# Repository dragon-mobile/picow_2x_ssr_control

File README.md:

# picow_ssr_control

<br/>

<br/>

The Raspberry Pi Pico W 2x Solid State Relay Controller is primarily meant to be
used with an open hardware solid state relay PCBs that is being co-developed
alongside this project as part of my Dragon Mobile GitHub organization to make
useful hardware with associated firmware and software for the tiny home, van
life and maker communities.

## Visual 3D examples

Top view<br/>
<br/>
Bottom view<br/>
<br/>

## Description

___Outdated___

~~The board consist of four main electronic sections: Power In / Control Out,
Power Management / Regulation, Manual Control,
and the PicoW Control / Drivers.
There is one mechanical section as well: Mounting Holes.~~

## Contributing

Contributors are welcome.
Please note that this project has a [Contributor Covenant Code of Conduct].
By participating in this project you agree to abide by its terms.

All intentionally contributed hardware will be considered to be contributed
under the [CERN] license without any additional terms or conditions.

All intentionally contributed code will be considered to be contributed
under a [MIT] license without any additional terms or conditions.
Please include your information in a comment on all code files for the copyright
etc.

All intentionally contributed documentation, CAD files and libraries, footprints,
artwork or non-code text like this README etc. will be considered to be
contributed under the same [CC-BY-SA] license without any additional terms or
conditions.

Pull requests are always welcome. For major changes, please open an issue first
to discuss what you would like to change.
Please make sure to update or add tests as appropriate for all software changes.

## Licenses

<br/>

All hardware is licensed under the

  * [CERN] - CERN-OHL-W-2.0
  
You can find a copy of the CERN Open Hardware License - Weakly-reciprocal v2.0
in the [LICENSE-CERN-OHL-W-2] file and the how-to guide in the
[CERN-HOWTO_GUIDE] file.

All code is licensed under the

  * [MIT] - MIT License

You can find a copy of the license in the [LICENSE-MIT] file.

All documentation like this README is licensed under the Creative Commons
Attribution-ShareAlike 4.0 International License (CC-BY-SA).

All original CAD files and libraries, footprints, and artwork are also licensed
under the
Creative Commons Attribution-ShareAlike 4.0 International License (CC-BY-SA).
You can find a copy of the [CC-BY-SA] license in the [LICENSE-CC-BY-SA] file.

If after reading the above license files, how-tos, and related FAQs on the
linked license sites on how they apply to the project please either open an
issue or contact me (Michael Cummings) via my Github email and I will try
to guided you through my understanding of how it works.

[CC-BY-SA]: http://creativecommons.org/licenses/by-sa/4.0/
[CERN]: https://ohwr.org/project/cernohl/wikis/Documents/CERN-OHL-version-2
[CERN-HOWTO_GUIDE]: docs/cern_ohl_w_v2_howto.pdf
[Contributor Covenant Code of Conduct]: CODE_OF_CONDUCT.md 
[LICENSE-CC-BY-SA]: LICENSE-CC-BY-SA
[LICENSE-CERN-OHL-W-2]: CERN-OHL-W-2
[LICENSE-MIT]: LICENSE-MIT
[MIT]: https://opensource.org/licenses/MIT

<hr>
Copyright &copy; 2023, Michael Cummings<br/>

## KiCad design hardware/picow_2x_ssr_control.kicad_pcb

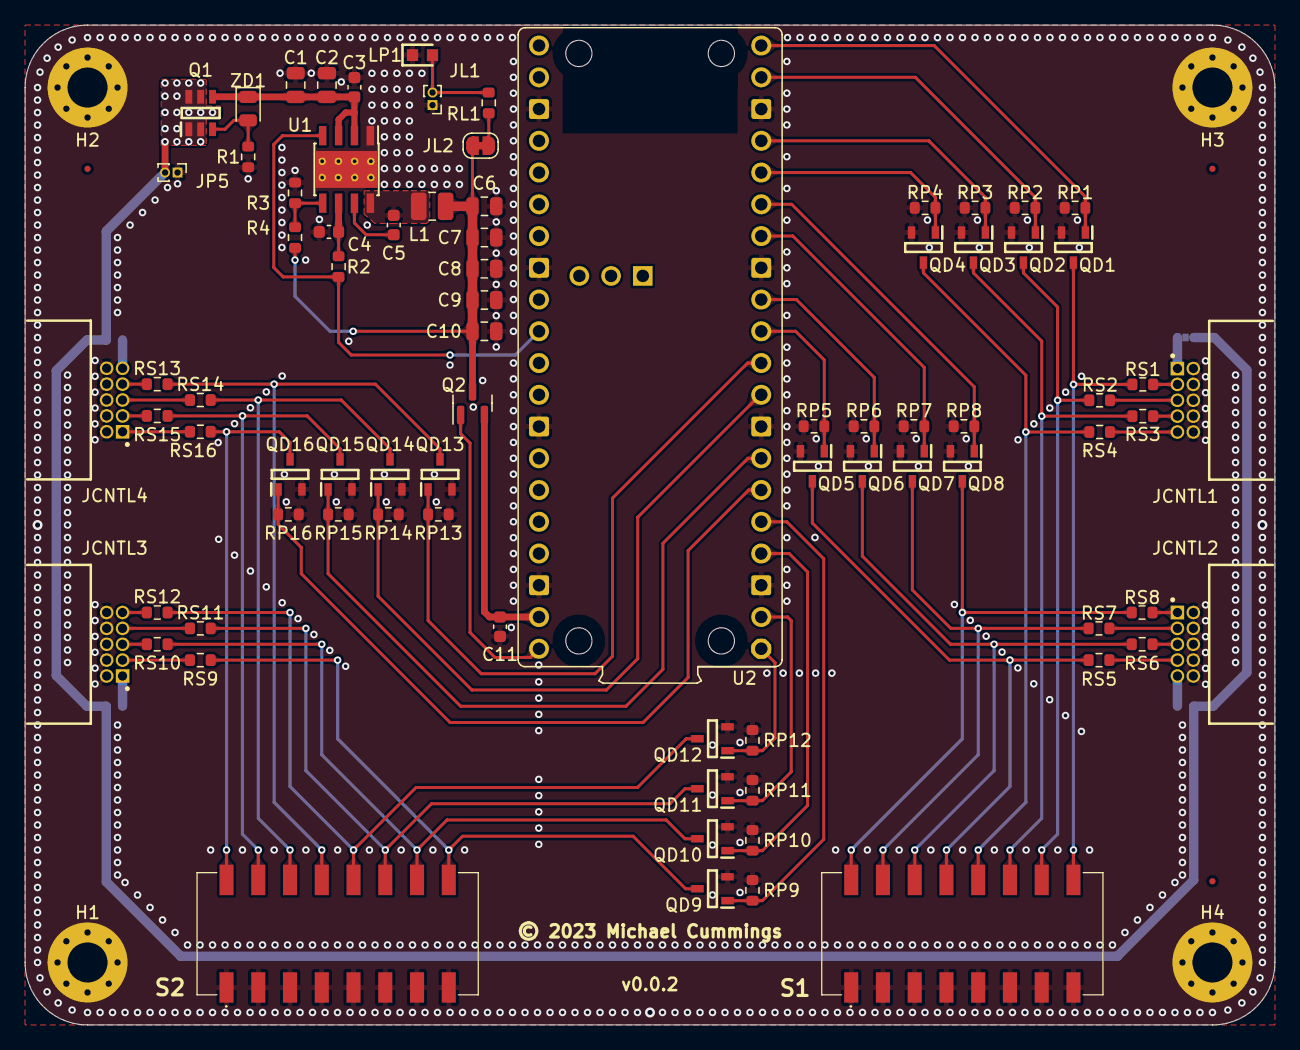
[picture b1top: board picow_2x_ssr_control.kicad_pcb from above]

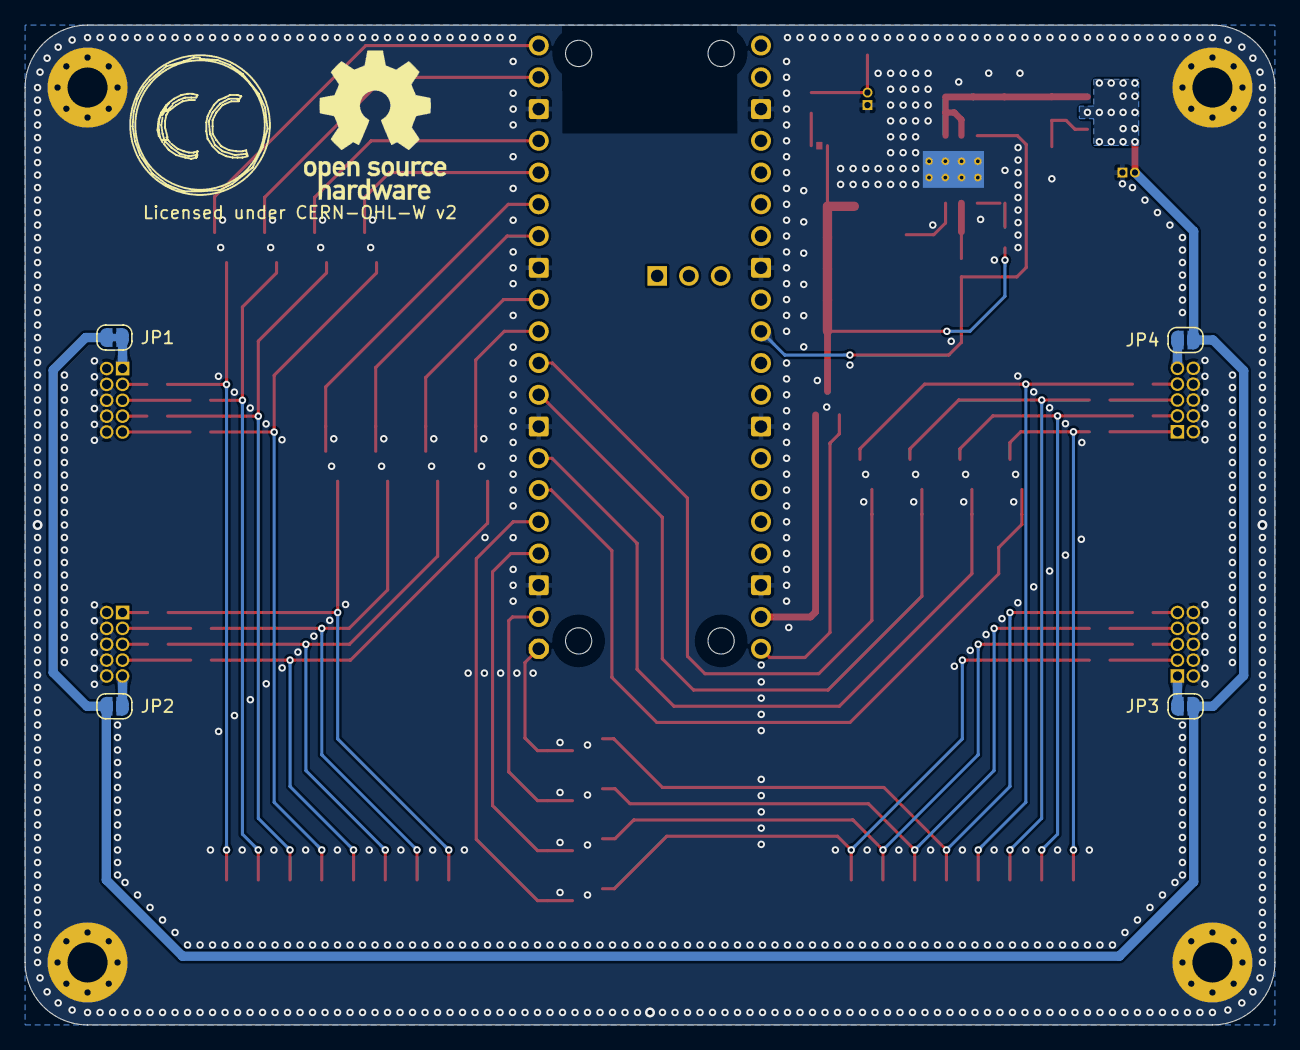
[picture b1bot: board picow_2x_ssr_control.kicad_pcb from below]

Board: 2 copper layers, 100.0 x 80.0 mm, 93 parts (4 on the bottom side), 66 nets.

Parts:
C1, C2, C6, C7, C8, C9, C10: 4u7; C_0805_2012Metric
C3: 220n; C_0603_1608Metric
C4: 1u; C_0603_1608Metric
C5, C11: 100n; C_0603_1608Metric
FID1, FID2, FID3: Fiducial; Fiducial_0.5mm_Mask1mm
H1, H2, H3, H4: MountingHole_Pad; MountingHole_3.2mm_M3_Pad_Via
JCNTL1, JCNTL2, JCNTL3, JCNTL4: SHF-105-01-L-D-RA; SAMTEC_SHF-105-01-L-D-RA
JCNTL1_Label: JCNTL1_Label
JCNTL2_Label: JCNTL2_Label
JL1: Conn_01x02; PinHeader_1x02_P1.00mm_Vertical
JL2: SolderJumper_2_Bridged; SolderJumper-2_P1.3mm_Bridged_RoundedPad1.0x1.5mm
JP1: SolderJumper_2_Bridged; SolderJumper-2_P1.3mm_Bridged_RoundedPad1.0x1.5mm
JP2, JP3, JP4: SolderJumper_2_Open; SolderJumper-2_P1.3mm_Open_RoundedPad1.0x1.5mm
JP5: Conn_01x02; PinHeader_1x02_P1.00mm_Vertical
L1: 2u2; L_1008_2520Metric
LP1: LTST-C190KGKT; LEDC1608X80N
Q1: SQ3419EV-T1_GE3; SOT95P284X110-6N
Q2: DMG2305UX-7; SOT-23
QD1, QD2, QD3, QD4, QD5, QD6, QD7, QD8, QD9, QD10, QD11, QD12, QD13, QD14, QD15, QD16: 2N7002K; 2V7002KT1G
R1, R2, R3: 100k; R_0603_1608Metric
R4: 24k9; R_0603_1608Metric
RL1: 270R; R_0603_1608Metric
RP1, RP2, RP3, RP4, RP5, RP6, RP7, RP8, RP9, RP10, RP11, RP12, RP13, RP14, RP15, RP16: 10k; R_0603_1608Metric
RS1, RS2, RS3, RS4, RS5, RS6, RS7, RS8, RS9, RS10, RS11, RS12, RS13, RS14, RS15, RS16: 270R; R_0603_1608Metric
S1, S2: 193-8MS; 1938MS
U1: LMR33610BDDAR; Texas_HSOP-8-1EP_3.9x4.9mm_P1.27mm_ThermalVias
U2: RaspberryPi-PicoW; Raspberry_Pi_Pico_THT
ZD1: 10V; D_0805_2012Metric

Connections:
+5V: C6.1, C7.1, C8.1, C9.1, C10.1, JL2.1 (A), L1.2, Q2.3 (D), R4.2
+BATT: JP1.2 (B), JP2.2 (B), JP3.2 (B), JP4.2 (B), JP5.2, Q1.1 (D), Q1.2 (D), Q1.5 (D), Q1.6 (D)
/Control Bank A/CNTL1: QD1.3 (D), RS1.1, S1.9
/Control Bank A/CNTL2: QD2.3 (D), RS2.1, S1.10
/Control Bank A/CNTL3: QD3.3 (D), RS3.1, S1.11
/Control Bank A/CNTL4: QD4.3 (D), RS4.1, S1.12
/Control Bank A/OUT1: JCNTL1.3, RS1.2
/Control Bank A/OUT2: JCNTL1.5, RS2.2
/Control Bank A/OUT3: JCNTL1.7, RS3.2
/Control Bank A/OUT4: JCNTL1.9, RS4.2
/Control Bank B/CNTL5: QD5.3 (D), RS5.1, S1.13
/Control Bank B/CNTL6: QD6.3 (D), RS6.1, S1.14
/Control Bank B/CNTL7: QD7.3 (D), RS7.1, S1.15
/Control Bank B/CNTL8: QD8.3 (D), RS8.1, S1.16
/Control Bank B/OUT5: JCNTL2.7, RS5.2
/Control Bank B/OUT6: JCNTL2.5, RS6.2
/Control Bank B/OUT7: JCNTL2.3, RS7.2
/Control Bank B/OUT8: JCNTL2.1, RS8.2
/Control Bank C/CNTL9: QD9.3 (D), RS9.1, S2.9
/Control Bank C/CNTL10: QD10.3 (D), RS10.1, S2.10
/Control Bank C/CNTL11: QD11.3 (D), RS11.1, S2.11
/Control Bank C/CNTL12: QD12.3 (D), RS12.1, S2.12
/Control Bank C/OUT9: JCNTL3.3, RS9.2
/Control Bank C/OUT10: JCNTL3.5, RS10.2
/Control Bank C/OUT11: JCNTL3.7, RS11.2
/Control Bank C/OUT12: JCNTL3.9, RS12.2
/Control Bank D/CNTL13: QD13.3 (D), RS13.1, S2.13
/Control Bank D/CNTL14: QD14.3 (D), RS14.1, S2.14
/Control Bank D/CNTL15: QD15.3 (D), RS15.1, S2.15
/Control Bank D/CNTL16: QD16.3 (D), RS16.1, S2.16
/Control Bank D/OUT13: JCNTL4.7, RS13.2
/Control Bank D/OUT14: JCNTL4.5, RS14.2
/Control Bank D/OUT15: JCNTL4.3, RS15.2
/Control Bank D/OUT16: JCNTL4.1, RS16.2
/Pico W Control/IO1: QD1.1 (G), RP1.1, U2.20 (GPIO15)
/Pico W Control/IO2: QD2.1 (G), RP2.1, U2.19 (GPIO14)
/Pico W Control/IO3: QD3.1 (G), RP3.1, U2.17 (GPIO13)
/Pico W Control/IO4: QD4.1 (G), RP4.1, U2.16 (GPIO12)
/Pico W Control/IO5: QD5.1 (G), RP5.1, U2.11 (GPIO8)
/Pico W Control/IO6: QD6.1 (G), RP6.1, U2.12 (GPIO9)
/Pico W Control/IO7: QD7.1 (G), RP7.1, U2.14 (GPIO10)
/Pico W Control/IO8: QD8.1 (G), RP8.1, U2.15 (GPIO11)
/Pico W Control/IO9: QD9.1 (G), RP9.1, U2.5 (GPIO3)
/Pico W Control/IO10: QD10.1 (G), RP10.1, U2.4 (GPIO2)
/Pico W Control/IO11: QD11.1 (G), RP11.1, U2.2 (GPIO1)
/Pico W Control/IO12: QD12.1 (G), RP12.1, U2.1 (GPIO0)
/Pico W Control/IO13: QD13.1 (G), RP13.1, U2.10 (GPIO7)
/Pico W Control/IO14: QD14.1 (G), RP14.1, U2.9 (GPIO6)
/Pico W Control/IO15: QD15.1 (G), RP15.1, U2.7 (GPIO5)
/Pico W Control/IO16: QD16.1 (G), RP16.1, U2.6 (GPIO4)
/Pico W Control/VBUS: Q2.1 (G), U2.40 (VBUS)
/Pico W Control/VSYS: C11.1, Q2.2 (S), U2.39 (VSYS)
/Power Management/BOOT: C5.1, U1.7 (BOOT)
/Power Management/FB: R3.1, R4.1, U1.5 (FB)
/Power Management/PI1: JCNTL1.1, JP1.1 (A)
/Power Management/PI2: JCNTL2.9, JP2.1 (A)
/Power Management/PI3: JCNTL3.1, JP3.1 (A)
/Power Management/PI4: JCNTL4.9, JP4.1 (A)
/Power Management/SW: C5.2, L1.1, U1.8 (SW)
/Power Management/VCC: C4.1, R2.1, U1.6 (VCC)
/Power Management/VDC: C1.1, C2.1, C3.1, Q1.4 (S), U1.2 (VIN), U1.3 (EN), ZD1.1
/Power Management/~PG: R2.2, U1.4 (PG), U2.30 (RUN)
GNDPWR: C1.2, C2.2, C3.2, C4.2, C6.2, C7.2, C8.2, C9.2, C10.2, C11.2, H1.1, H2.1, H3.1, H4.1, JCNTL1.2, JCNTL1.4, JCNTL1.6, JCNTL1.8, JCNTL1.10, JCNTL2.2, JCNTL2.4, JCNTL2.6, JCNTL2.8, JCNTL2.10, JCNTL3.2, JCNTL3.4, JCNTL3.6, JCNTL3.8, JCNTL3.10, JCNTL4.2, JCNTL4.4, JCNTL4.6, JCNTL4.8, JCNTL4.10, JL1.1, JP5.1, LP1.1, QD1.2 (S), QD2.2 (S), QD3.2 (S), QD4.2 (S), QD5.2 (S), QD6.2 (S), QD7.2 (S), QD8.2 (S), QD9.2 (S), QD10.2 (S), QD11.2 (S), QD12.2 (S), QD13.2 (S), QD14.2 (S), QD15.2 (S), QD16.2 (S), R1.2, R3.2, RP1.2, RP2.2, RP3.2, RP4.2, RP5.2, RP6.2, RP7.2, RP8.2, RP9.2, RP10.2, RP11.2, RP12.2, RP13.2, RP14.2, RP15.2, RP16.2, S1.1, S1.2, S1.3, S1.4, S1.5, S1.6, S1.7, S1.8, S2.1, S2.2, S2.3, S2.4, S2.5, S2.6, S2.7, S2.8, U1.1 (PGND), U1.9 (AGND), U2.3 (GND), U2.8 (GND), U2.13 (GND), U2.18 (GND), U2.23 (GND), U2.28 (GND), U2.33 (AGND), U2.38 (GND)
unnamed: JL1.2, LP1.2, RL1.2
unnamed: JL2.2 (B), RL1.1
unnamed: Q1.3 (G), R1.1, ZD1.2

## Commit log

2023-03-16 Add KiCAD files to hardware/
2023-03-16 Updated for outdated info in README.md
2023-03-16 Updated copyright year in README.md
2023-03-16 Added stuff to docs/ for README.md

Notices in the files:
README.md:
https://img.shields.io/static/v1?label=license&message=CERN-OHL-W-2.0%20%2F%20MIT%20%2F%20CC-BY-SA-4.0&color=orange
CC BY-SA 4.0
hardware/picow_2x_ssr_control.kicad_pcb:
Hardware License: CERN-OHL-W
https://creativecommons.org/licenses/by-sa/4.0
License: CC By SA 4.0
Licensed under CERN-OHL-W v2
© 2023 ${COMPANY}
